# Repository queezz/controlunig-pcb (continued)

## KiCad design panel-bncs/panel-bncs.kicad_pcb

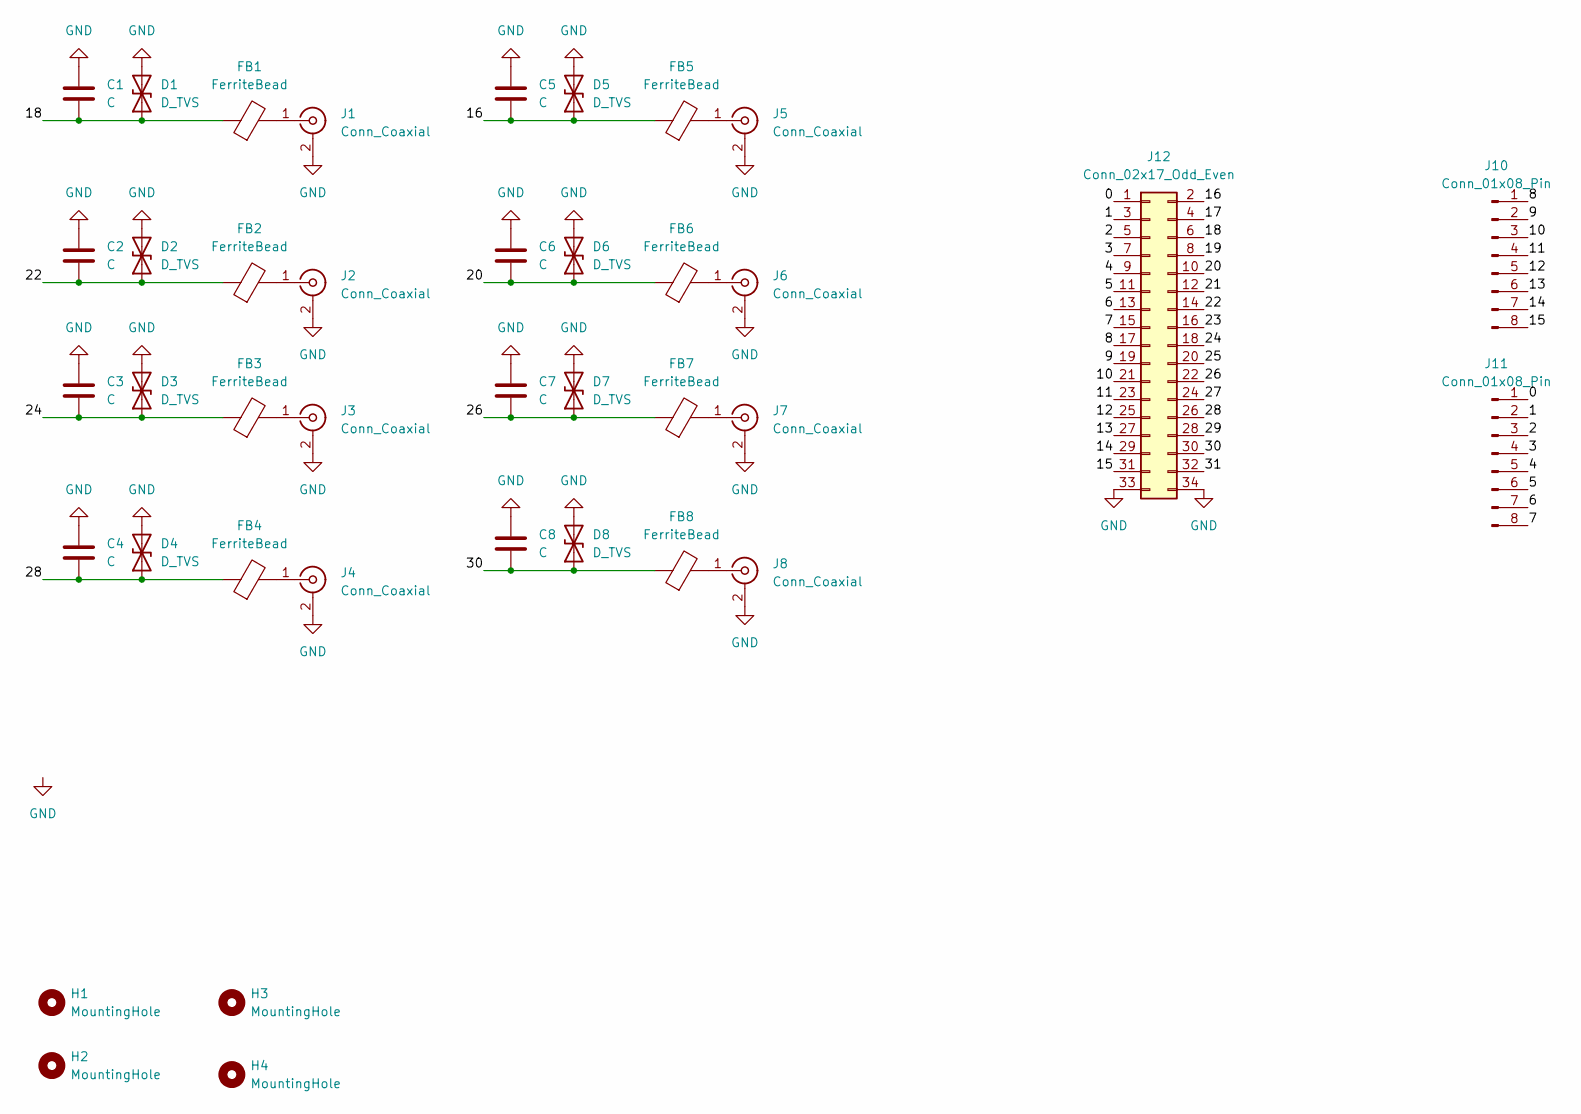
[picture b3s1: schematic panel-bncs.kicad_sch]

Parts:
C1, C2, C3, C4, C5, C6, C7, C8: C; C_0603_1608Metric
D1, D2, D3, D4, D5, D6, D7, D8: D_TVS; D_SOD-323_HandSoldering
FB1, FB2, FB3, FB4, FB5, FB6, FB7, FB8: FerriteBead; R_0603_1608Metric
H1, H2, H3, H4: MountingHole; MountingHole_3.2mm_M3_DIN965_Pad
J1, J2, J3, J4, J5, J6, J7, J8: Conn_Coaxial; BNC_TEConnectivity_1478204_Vertical
J10, J11: Conn_01x08_Pin; TerminalBlock_Phoenix_MPT-0,5-8-2.54_1x08_P2.54mm_Horizontal
J12: Conn_02x17_Odd_Even; IDC-Header_2x17_P2.54mm_Vertical

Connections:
/0: J11.1, J12.1
/1: J11.2, J12.3
/2: J11.3, J12.5
/3: J11.4, J12.7
/4: J11.5, J12.9
/5: J11.6, J12.11
/6: J11.7, J12.13
/7: J11.8, J12.15
/8: J10.1, J12.17
/9: J10.2, J12.19
/10: J10.3, J12.21
/11: J10.4, J12.23
/12: J10.5, J12.25
/13: J10.6, J12.27
/14: J10.7, J12.29
/15: J10.8, J12.31
/16: C5.2, D5.1 (A1), FB5.1, J12.2
/17: J12.4
/18: C1.2, D1.1 (A1), FB1.1, J12.6
/19: J12.8
/20: C6.2, D6.1 (A1), FB6.1, J12.10
/21: J12.12
/22: C2.2, D2.1 (A1), FB2.1, J12.14
/23: J12.16
/24: C3.2, D3.1 (A1), FB3.1, J12.18
/25: J12.20
/26: C7.2, D7.1 (A1), FB7.1, J12.22
/27: J12.24
/28: C4.2, D4.1 (A1), FB4.1, J12.26
/29: J12.28
/30: C8.2, D8.1 (A1), FB8.1, J12.30
/31: J12.32
GND: C1.1, C2.1, C3.1, C4.1, C5.1, C6.1, C7.1, C8.1, D1.2 (A2), D2.2 (A2), D3.2 (A2), D4.2 (A2), D5.2 (A2), D6.2 (A2), D7.2 (A2), D8.2 (A2), J1.2 (Ext), J2.2 (Ext), J3.2 (Ext), J4.2 (Ext), J5.2 (Ext), J6.2 (Ext), J7.2 (Ext), J8.2 (Ext), J12.33, J12.34
unnamed: FB1.2, J1.1 (In)
unnamed: FB2.2, J2.1 (In)
unnamed: FB3.2, J3.1 (In)
unnamed: FB4.2, J4.1 (In)
unnamed: FB5.2, J5.1 (In)
unnamed: FB6.2, J6.1 (In)
unnamed: FB7.2, J7.1 (In)
unnamed: FB8.2, J8.1 (In)

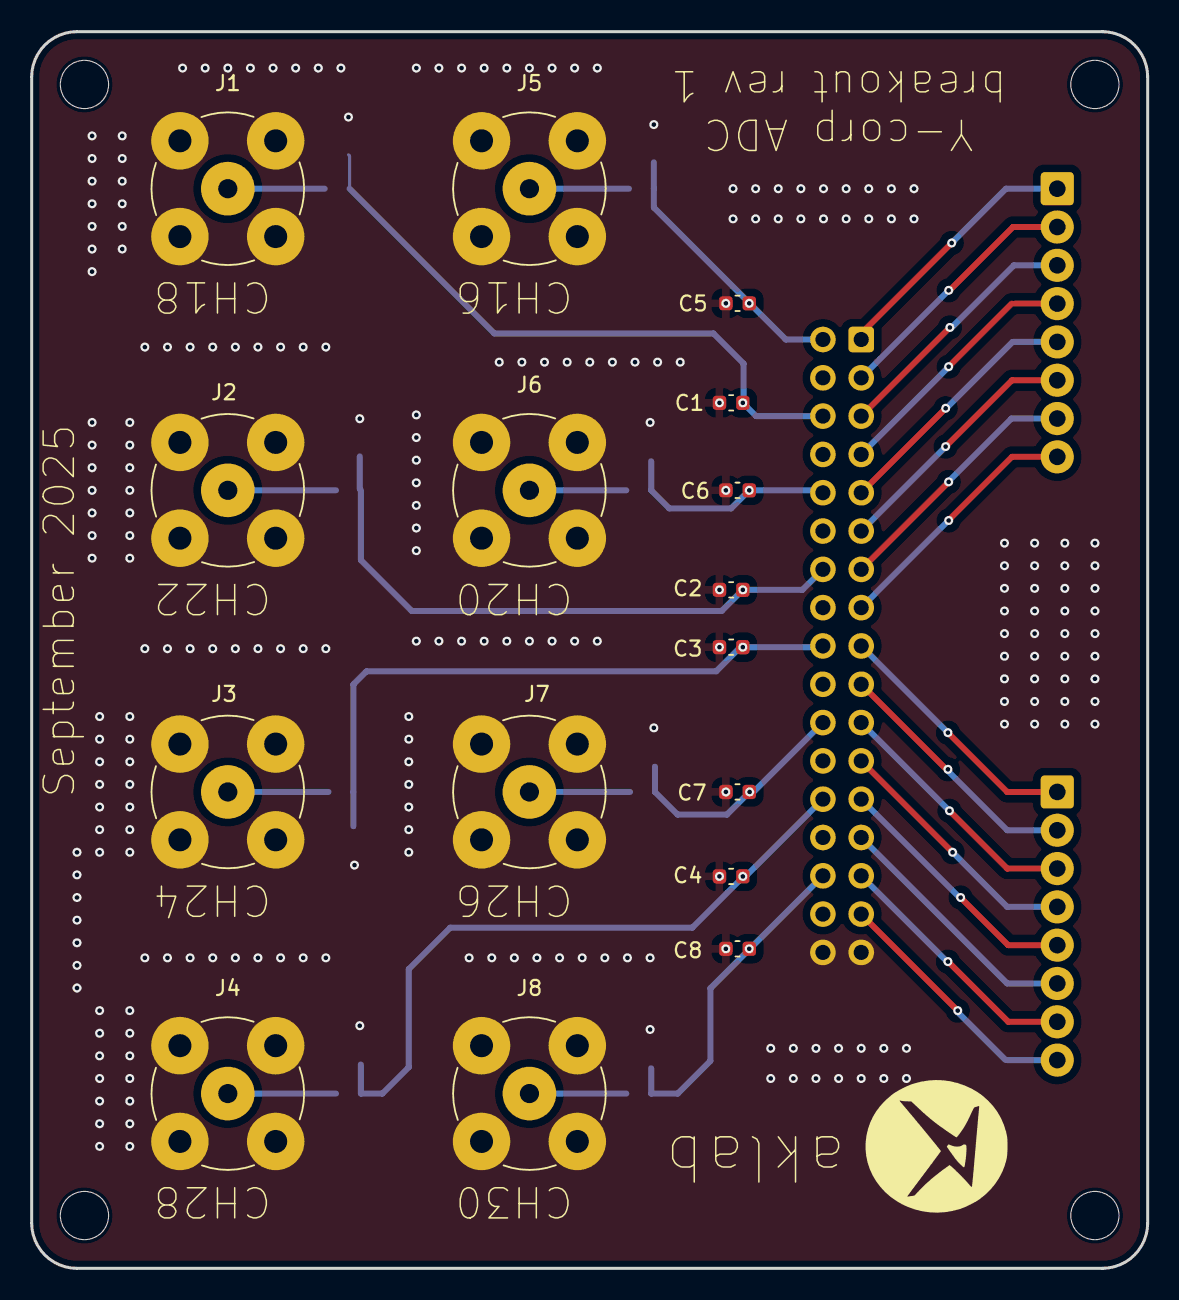
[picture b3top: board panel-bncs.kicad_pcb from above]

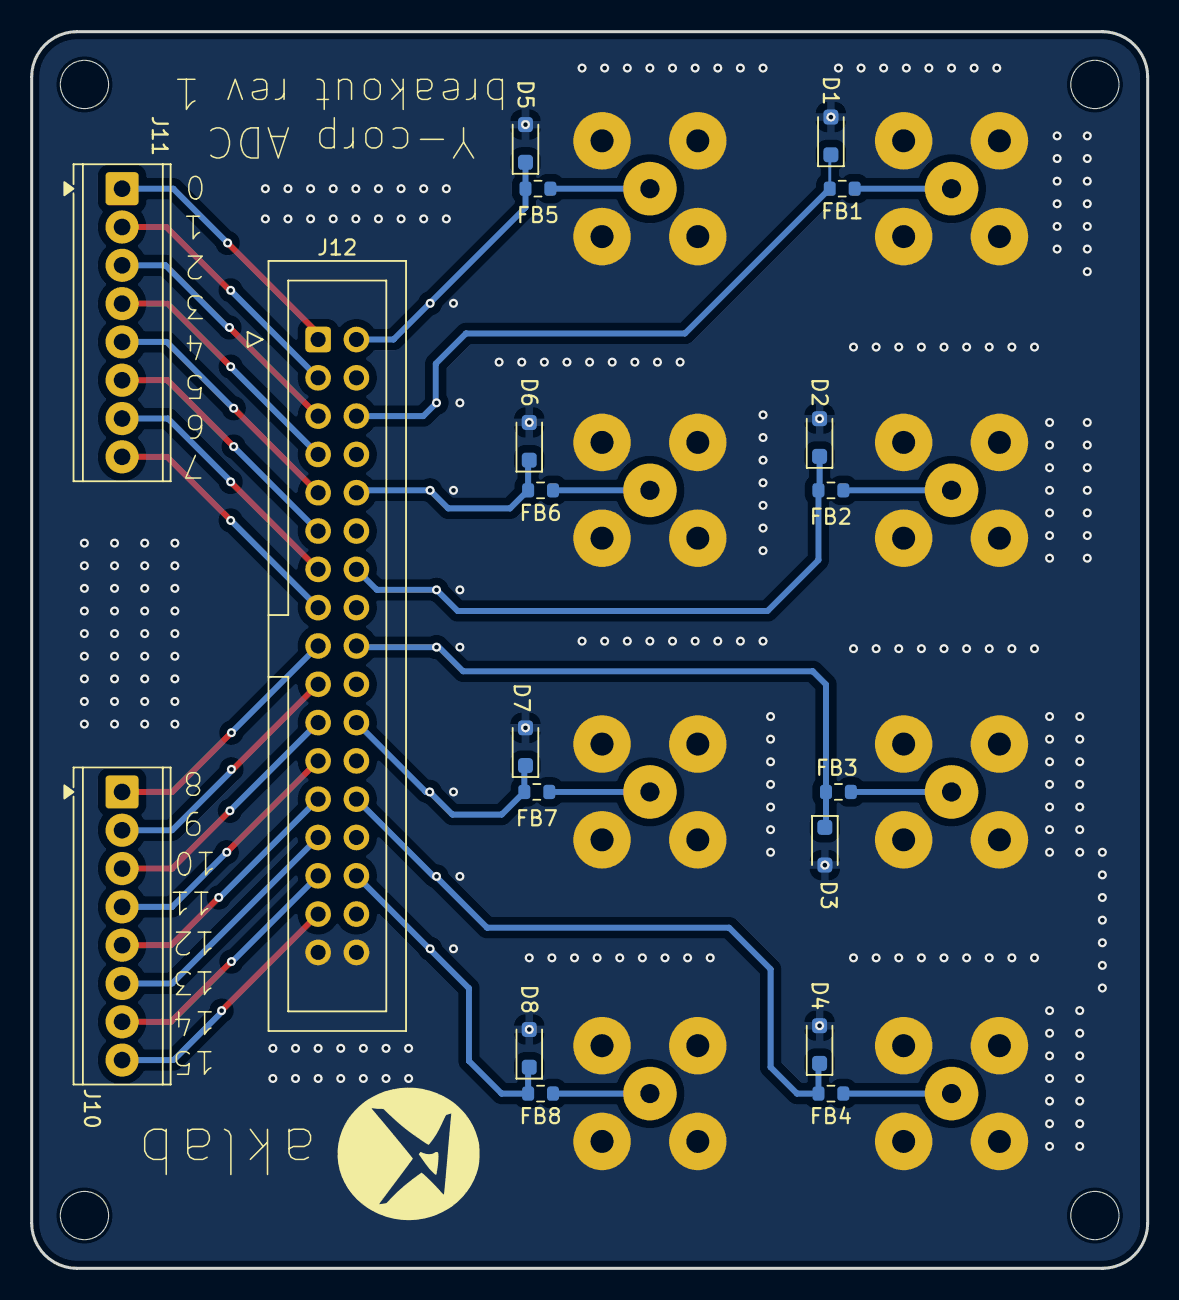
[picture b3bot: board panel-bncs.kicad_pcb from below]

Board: 2 copper layers, 74.0 x 82.0 mm, 39 parts (19 on the bottom side), 33 nets.

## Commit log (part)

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2025-09-13 pihat and ADC pane rev 1 version
2025-10-12 fix(0.1uF->100nF)
